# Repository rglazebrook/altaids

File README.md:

This is a repository for the new-retro single board computer [Altaids](https://www.nutsvolts.com/magazine/article/build-a-pocket-sized-altair-computer), designed by David Hunter. 

The Altaids is a single-board reimagining of the Altair 8800, running on the ever-so-slightly more modern Intel 8085, running at 2.5MHz with 8KB ROM and 8KB RAM. It has its own assembly monitor, its own variant of Palo Alto Tiny BASIC, and can save/load files via its terminal connection.

Oh -- and it fits inside of an Altoids tin.

Mostly, this is a place for me to store programs that I write for it.

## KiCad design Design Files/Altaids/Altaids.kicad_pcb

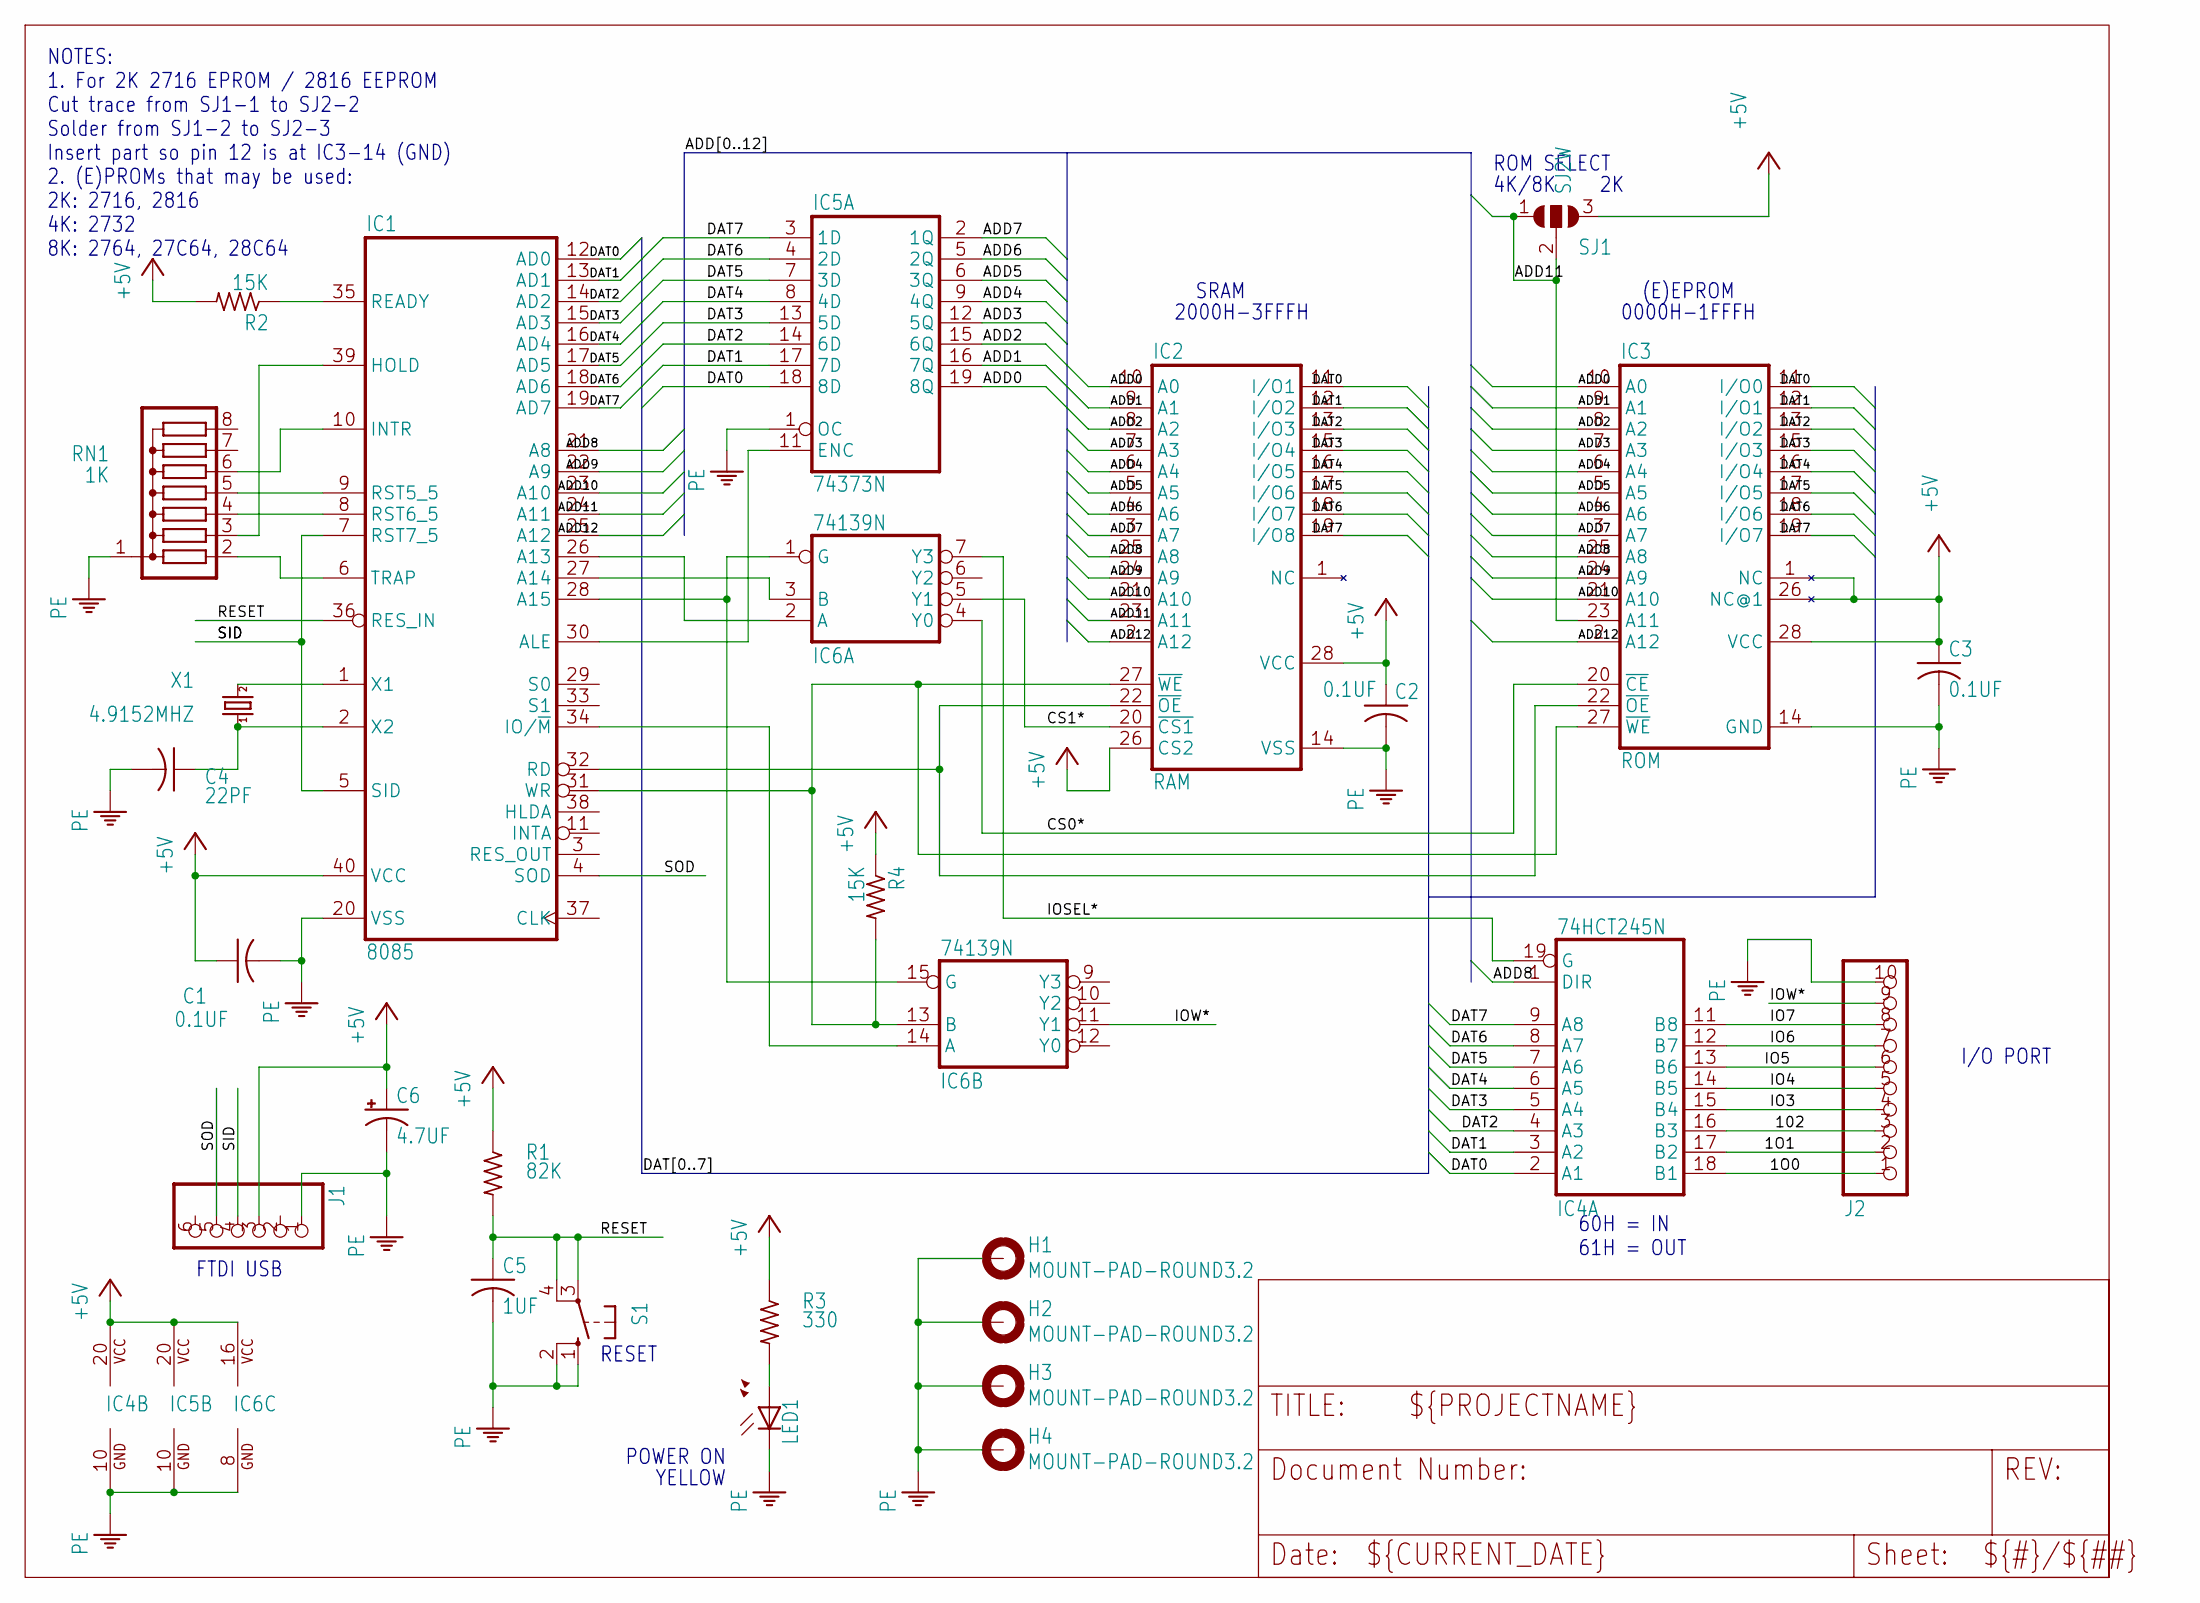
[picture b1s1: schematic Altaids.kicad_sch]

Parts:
C1, C2, C3: 0.1UF; C025-025X050
C4: 22PF; C025-025X050
C5: 1UF; C025-025X050
C6: 4.7UF; CPOL-RADIAL-100UF-25V
H1, H2, H3, H4: MOUNT-PAD-ROUND3.2; 3,2-PAD
IC1: 8085; DIL40
IC2: RAM; DIL28-6
IC3: ROM; DIL28-6
IC4: 74HCT245N; DIL20
IC5: 74373N; DIL20
IC6: 74139N; DIL16
J1: PINHD-1X6; 1X06
J2: PINHD-1X10; 1X10
LED1: LED3MM
R1: 82K; 0207_10
R2, R4: 15K; 0207_10
R3: 330; 0207_10
RN1: 1K; SIL8
S1: 10-XX; B3F-10XX
SJ1: SJ2W; SJ_2
X1: 4.9152MHZ; HC49U-H

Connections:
1O0: IC4.18 (B1), J2.1
1O1: IC4.17 (B2), J2.2
102: IC4.16 (B3), J2.3
+5V: C1.1, C2.1, C3.1, C6.1 (+), IC1.40 (VCC), IC2.26 (CS2), IC2.28 (VCC), IC3.1 (NC), IC3.26 (NC@1), IC3.28 (VCC), IC4.20 (VCC), IC5.20 (VCC), IC6.16 (VCC), J1.3, R1.1, R2.2, R3.1, R4.1, SJ1.3
ADD0: IC2.10 (A0), IC3.10 (A0), IC5.19 (8Q)
ADD1: IC2.9 (A1), IC3.9 (A1), IC5.16 (7Q)
ADD2: IC2.8 (A2), IC3.8 (A2), IC5.15 (6Q)
ADD3: IC2.7 (A3), IC3.7 (A3), IC5.12 (5Q)
ADD4: IC2.6 (A4), IC3.6 (A4), IC5.9 (4Q)
ADD5: IC2.5 (A5), IC3.5 (A5), IC5.6 (3Q)
ADD6: IC2.4 (A6), IC3.4 (A6), IC5.5 (2Q)
ADD7: IC2.3 (A7), IC3.3 (A7), IC5.2 (1Q)
ADD8: IC1.21 (A8), IC2.25 (A8), IC3.25 (A8), IC4.1 (DIR)
ADD9: IC1.22 (A9), IC2.24 (A9), IC3.24 (A9)
ADD10: IC1.23 (A10), IC2.21 (A10), IC3.21 (A10)
ADD11: IC1.24 (A11), IC2.23 (A11), IC3.23 (A11), SJ1.1, SJ1.2
ADD12: IC1.25 (A12), IC2.2 (A12), IC3.2 (A12)
CS0*: IC3.20 (~CE), IC6.4 (Y0)
CS1*: IC2.20 (~CS1), IC6.5 (Y1)
DAT0: IC1.12 (AD0), IC2.11 (I/O1), IC3.11 (I/O0), IC4.2 (A1), IC5.18 (8D)
DAT1: IC1.13 (AD1), IC2.12 (I/O2), IC3.12 (I/O1), IC4.3 (A2), IC5.17 (7D)
DAT2: IC1.14 (AD2), IC2.13 (I/O3), IC3.13 (I/O2), IC4.4 (A3), IC5.14 (6D)
DAT3: IC1.15 (AD3), IC2.15 (I/O4), IC3.15 (I/O3), IC4.5 (A4), IC5.13 (5D)
DAT4: IC1.16 (AD4), IC2.16 (I/O5), IC3.16 (I/O4), IC4.6 (A5), IC5.8 (4D)
DAT5: IC1.17 (AD5), IC2.17 (I/O6), IC3.17 (I/O5), IC4.7 (A6), IC5.7 (3D)
DAT6: IC1.18 (AD6), IC2.18 (I/O7), IC3.18 (I/O6), IC4.8 (A7), IC5.4 (2D)
DAT7: IC1.19 (AD7), IC2.19 (I/O8), IC3.19 (I/O7), IC4.9 (A8), IC5.3 (1D)
IO3: IC4.15 (B4), J2.4
IO4: IC4.14 (B5), J2.5
IO5: IC4.13 (B6), J2.6
IO6: IC4.12 (B7), J2.7
IO7: IC4.11 (B8), J2.8
IOSEL*: IC4.19 (G), IC6.7 (Y3)
IOW*: IC6.11 (Y1), J2.9
unnamed: IC1.35 (READY), R2.1
unnamed: IC1.39 (HOLD), RN1.3
unnamed: IC1.10 (INTR), RN1.6
unnamed: IC1.9 (RST5_5), RN1.5
unnamed: IC1.8 (RST6_5), RN1.4
unnamed: IC1.6 (TRAP), RN1.2
unnamed: IC1.28 (A15), IC6.1 (G), IC6.15 (G)
unnamed: IC1.31 (WR), IC2.27 (~WE), IC3.27 (~WE), IC6.13 (B), R4.2
unnamed: LED1.A, R3.2
unnamed: C4.1, IC1.2 (X2), X1.1
unnamed: IC1.1 (X1), X1.2
unnamed: IC1.34 (IO/~M), IC6.14 (A)
unnamed: IC1.30 (ALE), IC5.11 (ENC)
unnamed: IC1.27 (A14), IC6.3 (B)
unnamed: IC1.26 (A13), IC6.2 (A)
unnamed: IC1.32 (RD), IC2.22 (~OE), IC3.22 (~OE)
PE: C1.2, C2.2, C3.2, C4.2, C5.2, C6.2 (-), H1.B3,2, H2.B3,2, H3.B3,2, H4.B3,2, IC1.20 (VSS), IC2.14 (VSS), IC3.14 (GND), IC4.10 (GND), IC5.1 (OC), IC5.10 (GND), IC6.8 (GND), J1.1, J2.10, LED1.K (C), RN1.1, S1.1 (S), S1.2 (S1)
RESET: C5.1, IC1.36 (RES_IN), R1.2, S1.3, S1.4 (P1)
SID: IC1.5 (SID), IC1.7 (RST7_5), J1.4
SOD: IC1.4 (SOD), J1.5

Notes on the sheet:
POWER ON
2000H-3FFFH
NOTES: 1. For 2K 2716 EPROM / 2816 EEPROM Cut trace from SJ1-1 to SJ2-2 Solder from SJ1-2 to SJ2-3 Insert part so pin 12 is at IC3-14 (GND) 2. (E)PROMs that may be used: 2K: 2716, 2816 4K: 2732 8K: 2764, 27C64, 28C64
ROM SELECT
0000H-1FFFH
60H = IN 61H = OUT
4K/8K
RESET
YELLOW
(E)EPROM
I/O PORT
SRAM
FTDI USB

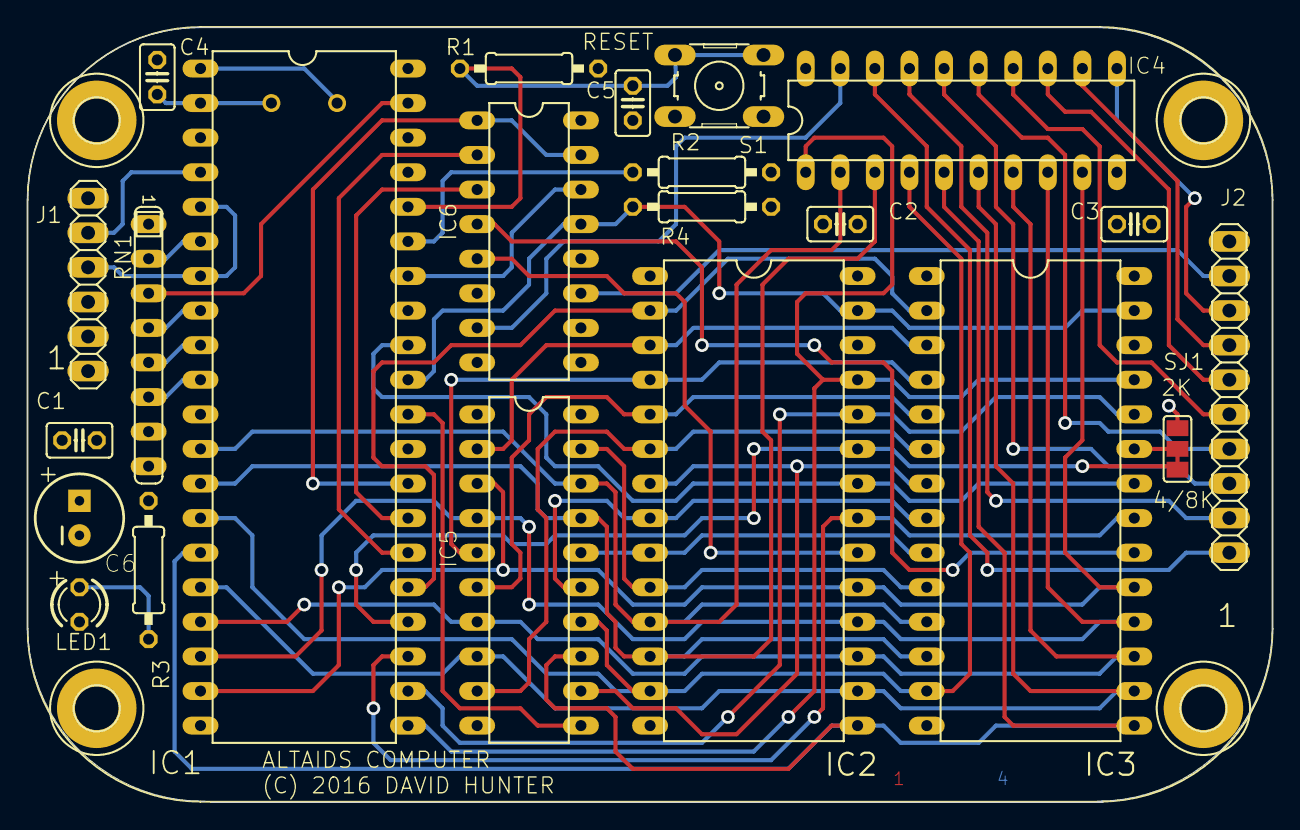
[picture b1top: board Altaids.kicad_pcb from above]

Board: 4 copper layers, 91.4 x 56.9 mm, 29 parts (1 on the bottom side), 54 nets.

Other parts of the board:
U$1, U$1#2: ALTOIDSTIN

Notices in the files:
Design Files/Altaids/Altaids.kicad_pcb:
(C) 2016 DAVID HUNTER
